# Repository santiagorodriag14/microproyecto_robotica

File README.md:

# Microproyecto Robótica: 
## Risky: Robot escalador teleoperado con adhesión por hélices para inspección de fisuras mediante sensor ToF

Este repositorio contiene el código fuente, diseños de hardware y documentación para el proyecto de investigación: **"Metrología de alta precisión de grietas mediante láser ToF con compensación inercial en tiempo real para teleoperación"**.

Para más detalles teóricos y metodológicos, puedes consultar el documento principal **Microproyecto Robótica** y el archivo **anteproyecto_herramienta.md** ubicados en la carpeta `docs/`.

## 📌 Descripción del Proyecto

En el ámbito de los sistemas ciber-físicos y los ensayos no destructivos (END), la inspección remota de infraestructuras críticas mediante plataformas robóticas se ve fuertemente afectada por vibraciones mecánicas y perturbaciones dinámicas de los motores BLDC. 

Este proyecto propone un marco metodológico estructurado para resolver estas incertidumbres métricas, integrando:
- Adquisición de datos por **láser Time-of-Flight (ToF)**.
- Telemetría inercial de alta frecuencia (IMU).

**Objetivo Principal:** Reducir el error métrico por debajo de 0.05 mm y mantener una latencia de lazo cerrado inferior a 5 ms en entornos teleoperados.

## 📂 Estructura del Repositorio

```text
📦 repositorio-robotica-tof
├── 📂 docs/             # Documentación, "Microproyecto Robótica" y "anteproyecto_herramienta.md"
├── 📂 hardware/         # Diseños CAD 3D y esquemas de los circuitos de sincronización
├── 📂 src/              # Código fuente (El "cerebro" del proyecto)
```

## 🛠️ Requisitos e Instalación

1. Clona este repositorio en tu máquina local:
   ```bash
   git clone https://github.com/santiagorodriag14/microproyecto_robotica.git
   cd repositorio-robotica-tof
   ```

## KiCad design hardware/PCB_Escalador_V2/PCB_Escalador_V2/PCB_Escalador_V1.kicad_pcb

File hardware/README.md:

# 🛠️ Hardware y Diseño (hardware/)

Este directorio está destinado a los recursos físicos, diseños 3D y componentes electrónicos del robot y los sensores.

## Estructura 
*   **`/CAD`**: Archivos de diseño 3D (archivos fuente como `.f3d`, `.sldprt` y exportables como `.stl`, `.step`) para la impresión o manufactura. 

*   **`/esquemas`**: Diagramas de circuitos (Schematics) y diseños de placas (PCB) necesarios para el bus de tiempo común y sincronización de hardware.

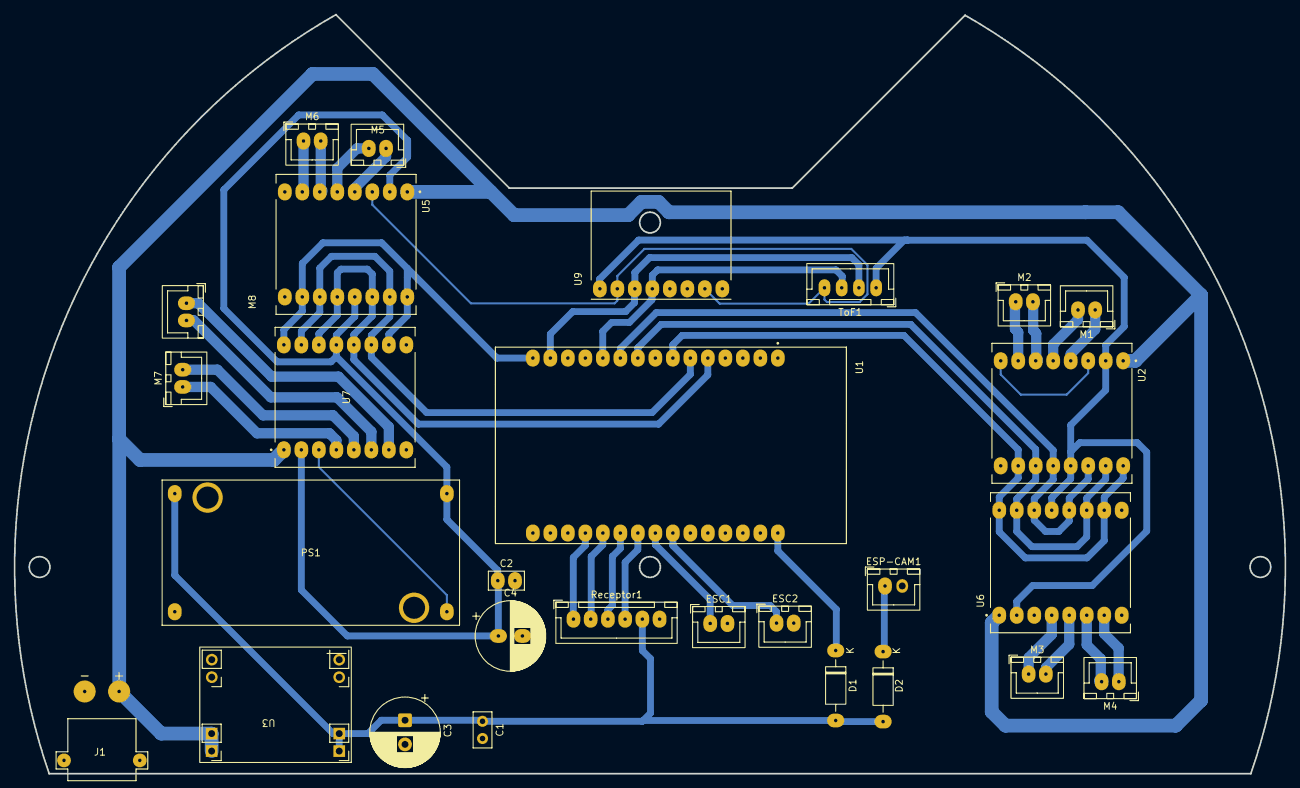
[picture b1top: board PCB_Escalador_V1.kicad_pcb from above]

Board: 2 copper layers, 184.5 x 110.2 mm, 28 parts (0 on the bottom side), 36 nets.

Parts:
C1, C2: C; C_Disc_D5.0mm_W2.5mm_P2.50mm
C3, C4: C_Polarized; CP_Radial_D10.0mm_P3.50mm
D1, D2: D; D_DO-41_SOD81_P10.16mm_Horizontal
ESC1, ESC2: Conn_01x02_Pin; JST_XH_B2B-XH-A_1x02_P2.50mm_Vertical
ESP-CAM1: Conn_01x02_Pin; JST_XH_B2B-XH-A_1x02_P2.50mm_Vertical
J1: XT30PW-M; AMASS_XT30PW-M
M1, M2, M3, M4, M5, M6, M7, M8: Conn_01x02_Pin; JST_XH_B2B-XH-A_1x02_P2.50mm_Vertical
PS1: MC00100; CONV_MC00100
Receptor1: Conn_01x06_Pin; JST_XH_B6B-XH-A_1x06_P2.50mm_Vertical
ToF1: Conn_01x04_Pin; JST_XH_B4B-XH-A_1x04_P2.50mm_Vertical
U1: DEVKIT_V1_ESP32-WROOM-32; MODULE_DEVKIT_V1_ESP32-WROOM-32
U2, U5, U6, U7: ROB-14450; TB6612FNG
U3: MP1584module
U9: OC09600; MODULE_OC09600

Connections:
/+3.3V: C2.1, C4.1, PS1.OUT+, ToF1.1, U2.2 (VCC), U2.13 (STBY), U5.2 (VCC), U5.13 (STBY), U6.2 (VCC), U6.13 (STBY), U7.2 (VCC), U7.13 (STBY), U9.VCC
/+5V: C1.1, C3.1, D1.2 (A), D2.2 (A), PS1.IN+, Receptor1.5, U3.4 (OUT+)
/+12V: J1.P, U2.1 (VM), U3.1 (IN+), U5.1 (VM), U6.1 (VM), U7.1 (VM)
/+M1: M1.1, U2.4 (A01)
/+M2: M2.1, U2.7 (B01)
/+M3: M3.1, U6.4 (A01)
/+M4: M4.1, U6.7 (B01)
/+M5: M5.1, U5.4 (A01)
/+M6: M6.1, U5.7 (B01)
/+M7: M7.1, U7.4 (A01)
/+M8: M8.1, U7.7 (B01)
/-M1: M1.2, U2.5 (A02)
/-M2: M2.2, U2.6 (B02)
/-M3: M3.2, U6.5 (A02)
/-M4: M4.2, U6.6 (B02)
/-M5: M5.2, U5.5 (A02)
/-M6: M6.2, U5.6 (B02)
/-M7: M7.2, U7.5 (A02)
/-M8: M8.2, U7.6 (B02)
/CH1_L: Receptor1.1, U1.19 (D34)
/CH3_L: Receptor1.2, U1.20 (D35)
/CH5_L: Receptor1.3, U1.21 (D32)
/CH6_L: Receptor1.4, U1.22 (D33)
/L_IN1: U1.10 (D19), U2.12 (BI1), U2.14 (AI1), U6.12 (BI1), U6.14 (AI1)
/L_IN2: U1.9 (D18), U2.11 (BI2), U2.15 (AI2), U6.11 (BI2), U6.15 (AI2)
/PWM_L: U1.7 (TX2), U2.10 (PWMB), U2.16 (PWMA), U6.10 (PWMB), U6.16 (PWMA)
/PWM_R: U1.15 (D23), U5.10 (PWMB), U5.16 (PWMA), U7.10 (PWMB), U7.16 (PWMA)
/R_IN1: U1.5 (D4), U5.12 (BI1), U5.14 (AI1), U7.12 (BI1), U7.14 (AI1)
/R_IN2: U1.6 (RX2), U5.11 (BI2), U5.15 (AI2), U7.11 (BI2), U7.15 (AI2)
/SCL: ToF1.2, U1.14 (D22), U9.SCL
/SDA: ToF1.3, U1.11 (D21), U9.SDA
/Señal_1: ESC1.1, U1.23 (D25)
/Señal_2: ESC2.1, U1.24 (D26)
GND: C1.2, C2.2, C3.2, C4.2, ESC1.2, ESC2.2, ESP-CAM1.2, J1.N, PS1.IN-, PS1.OUT-, Receptor1.6, ToF1.4, U1.2 (GND), U1.29 (GND), U2.3 (GND), U2.8 (GND), U2.9 (GND), U3.2 (IN-), U3.3 (OUT-), U5.3 (GND), U5.8 (GND), U5.9 (GND), U6.3 (GND), U6.8 (GND), U6.9 (GND), U7.3 (GND), U7.8 (GND), U7.9 (GND), U9.AD0, U9.GND
unnamed: D1.1 (K), U1.30 (VIN)
unnamed: D2.1 (K), ESP-CAM1.1
